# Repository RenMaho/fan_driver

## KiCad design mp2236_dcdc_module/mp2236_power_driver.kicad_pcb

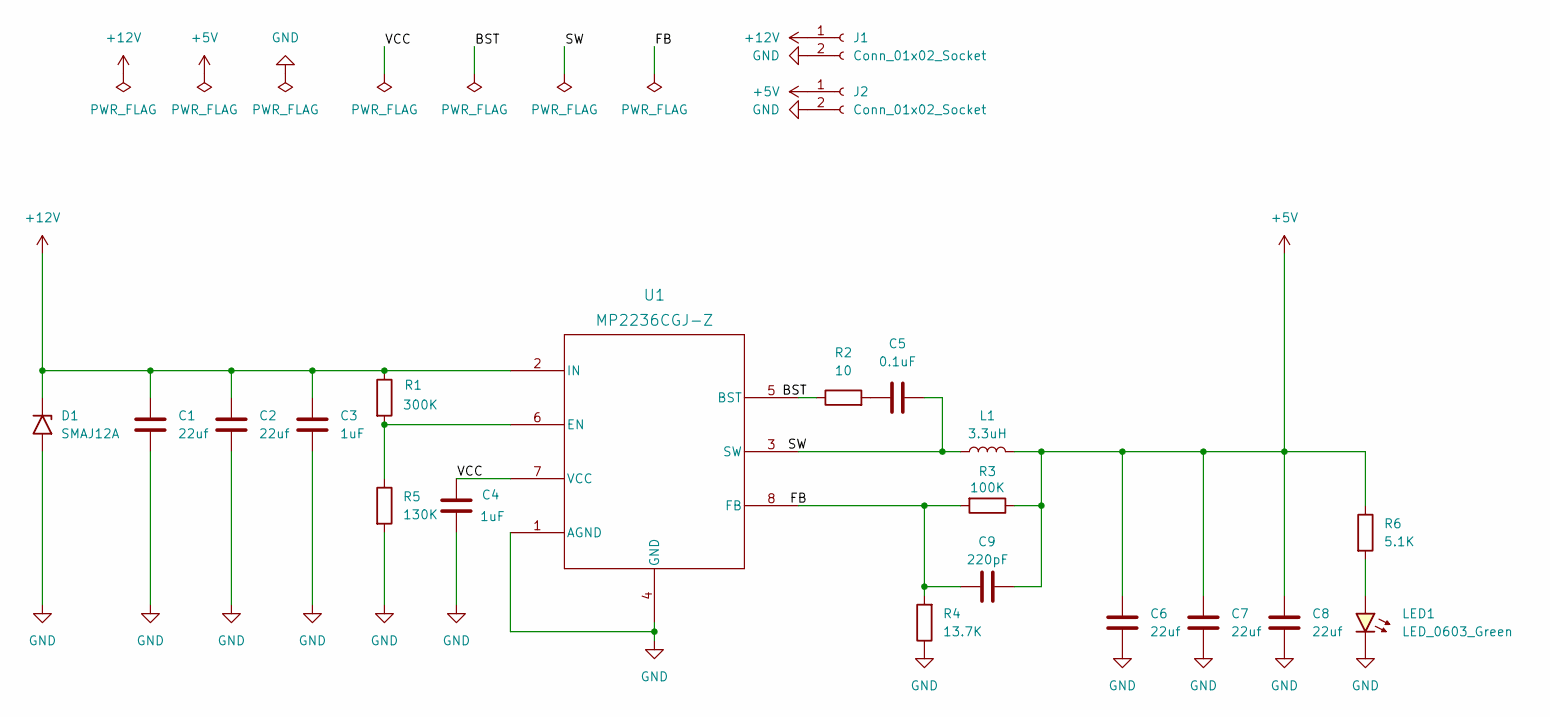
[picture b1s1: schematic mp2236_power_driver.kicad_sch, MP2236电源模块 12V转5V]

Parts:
C1, C2: 22uf; C_1206_3216Metric
C3, C4: 1uF; C_0603_1608Metric
C5: 0.1uF; C_0603_1608Metric
C6, C7, C8: 22uf; C_0805_2012Metric
C9: 220pF; C_0603_1608Metric
D1: SMAJ12A; D_SMA
J1, J2: Conn_01x02_Socket; 4mmx5mm_2x18.0mm power pad
L1: 3.3uH; L_Abracon_ASPI-0630LR
LED1: LED_0603_Green; LED_0603_1608Metric
R1: 300K; R_0603_1608Metric
R2: 10; R_0603_1608Metric
R3: 100K; R_0603_1608Metric
R4: 13.7K; R_0603_1608Metric
R5: 130K; R_0603_1608Metric
R6: 5.1K; R_0603_1608Metric
U1: MP2236CGJ-Z; TSOT-23-8

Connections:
+5V: C6.1, C7.1, C8.1, C9.1, J2.1, L1.2, R3.1, R6.1
+12V: C1.1, C2.1, C3.1, D1.1 (A1), J1.1, R1.1, U1.2 (IN)
/BST: R2.1, U1.5 (BST)
/FB: C9.2, R3.2, R4.2, U1.8 (FB)
/SW: C5.2, L1.1, U1.3 (SW)
/VCC: C4.2, U1.7 (VCC)
GND: C1.2, C2.2, C3.2, C4.1, C6.2, C7.2, C8.2, D1.2 (A2), J1.2, J2.2, LED1.1 (K), R4.1, R5.2, U1.1 (AGND), U1.4 (GND)
unnamed: C5.1, R2.2
unnamed: LED1.2 (A), R6.2
unnamed: R1.2, R5.1, U1.6 (EN)

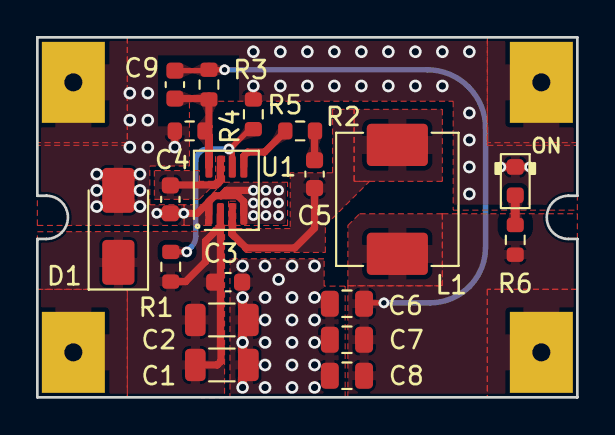
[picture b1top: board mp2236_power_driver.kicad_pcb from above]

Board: 2 copper layers, 30.0 x 20.0 mm, 21 parts (0 on the bottom side), 10 nets.

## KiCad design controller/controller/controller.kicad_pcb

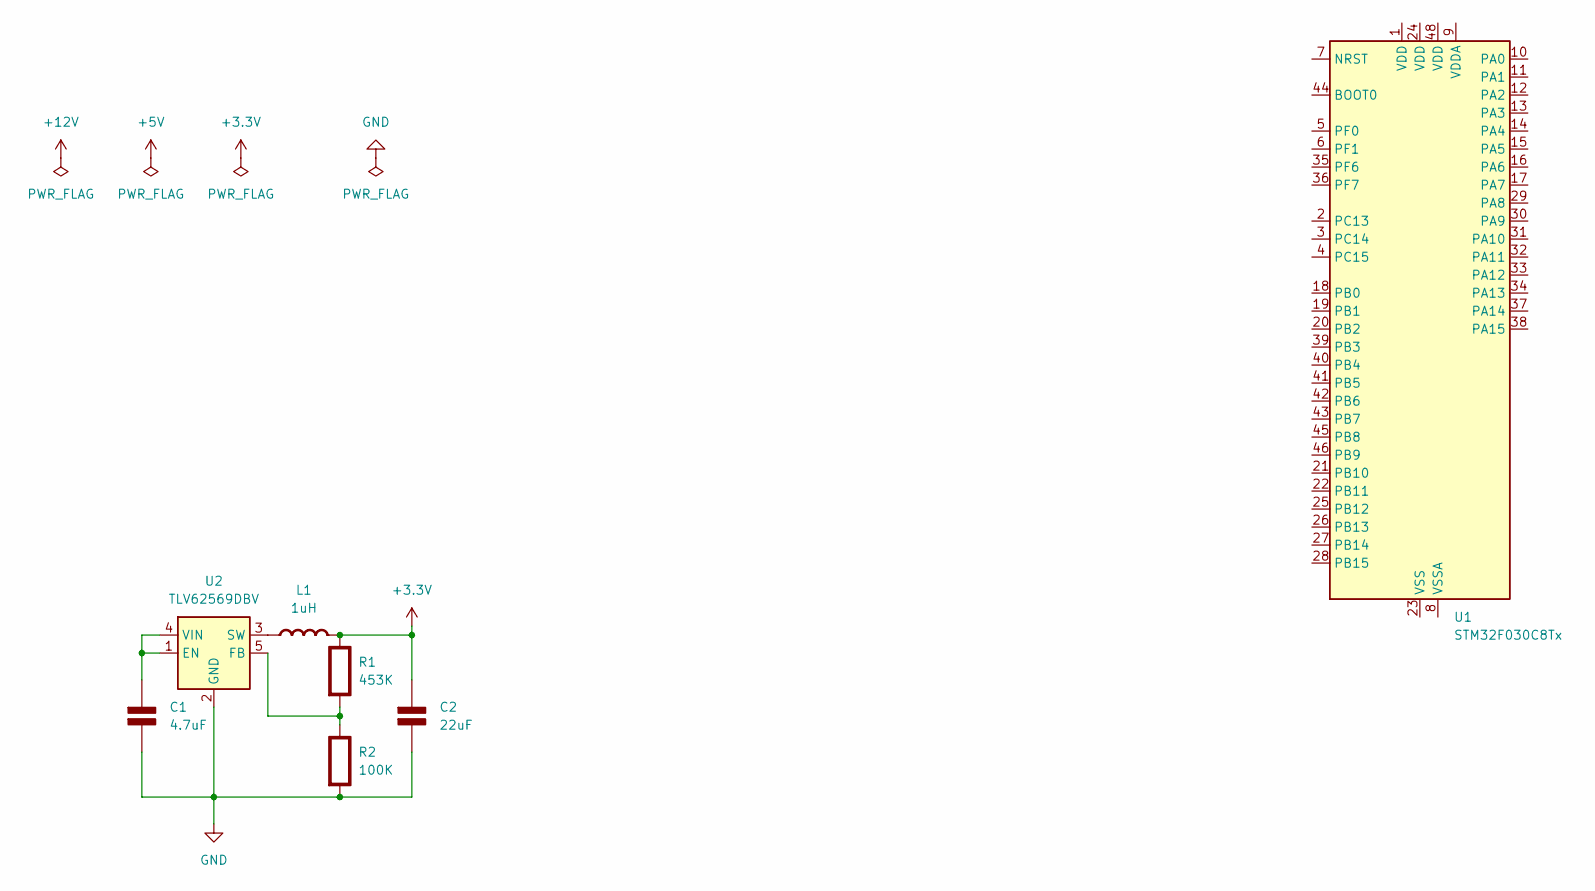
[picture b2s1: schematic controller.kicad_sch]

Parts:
C1: 4.7uF; C_0805_2012Metric_Pad1.18x1.45mm_HandSolder; Rating V
C2: 22uF; C_0805_2012Metric_Pad1.18x1.45mm_HandSolder; Rating V
L1: 1uH; L_Abracon_ASPI-0630LR; Rating A
R1: 453K; R_0603_1608Metric_Pad0.98x0.95mm_HandSolder; Rating W
R2: 100K; R_0603_1608Metric_Pad0.98x0.95mm_HandSolder; Rating W
U1: STM32F030C8Tx; LQFP-48_7x7mm_P0.5mm
U2: TLV62569DBV; SOT-23-5

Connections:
+3.3V: C2.1 (+), L1.2 (-), R1.1 (+)
GND: C1.2 (-), C2.2 (-), R2.2 (-), U2.2 (GND)
unnamed: C1.1 (+), U2.1 (EN), U2.4 (VIN)
unnamed: L1.1 (+), U2.3 (SW)
unnamed: R1.2 (-), R2.1 (+), U2.5 (FB)
unnamed: U1.23 (VSS), U1.47 (VSS)

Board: 2 copper layers, 7 parts (0 on the bottom side), 6 nets, no tracks yet.

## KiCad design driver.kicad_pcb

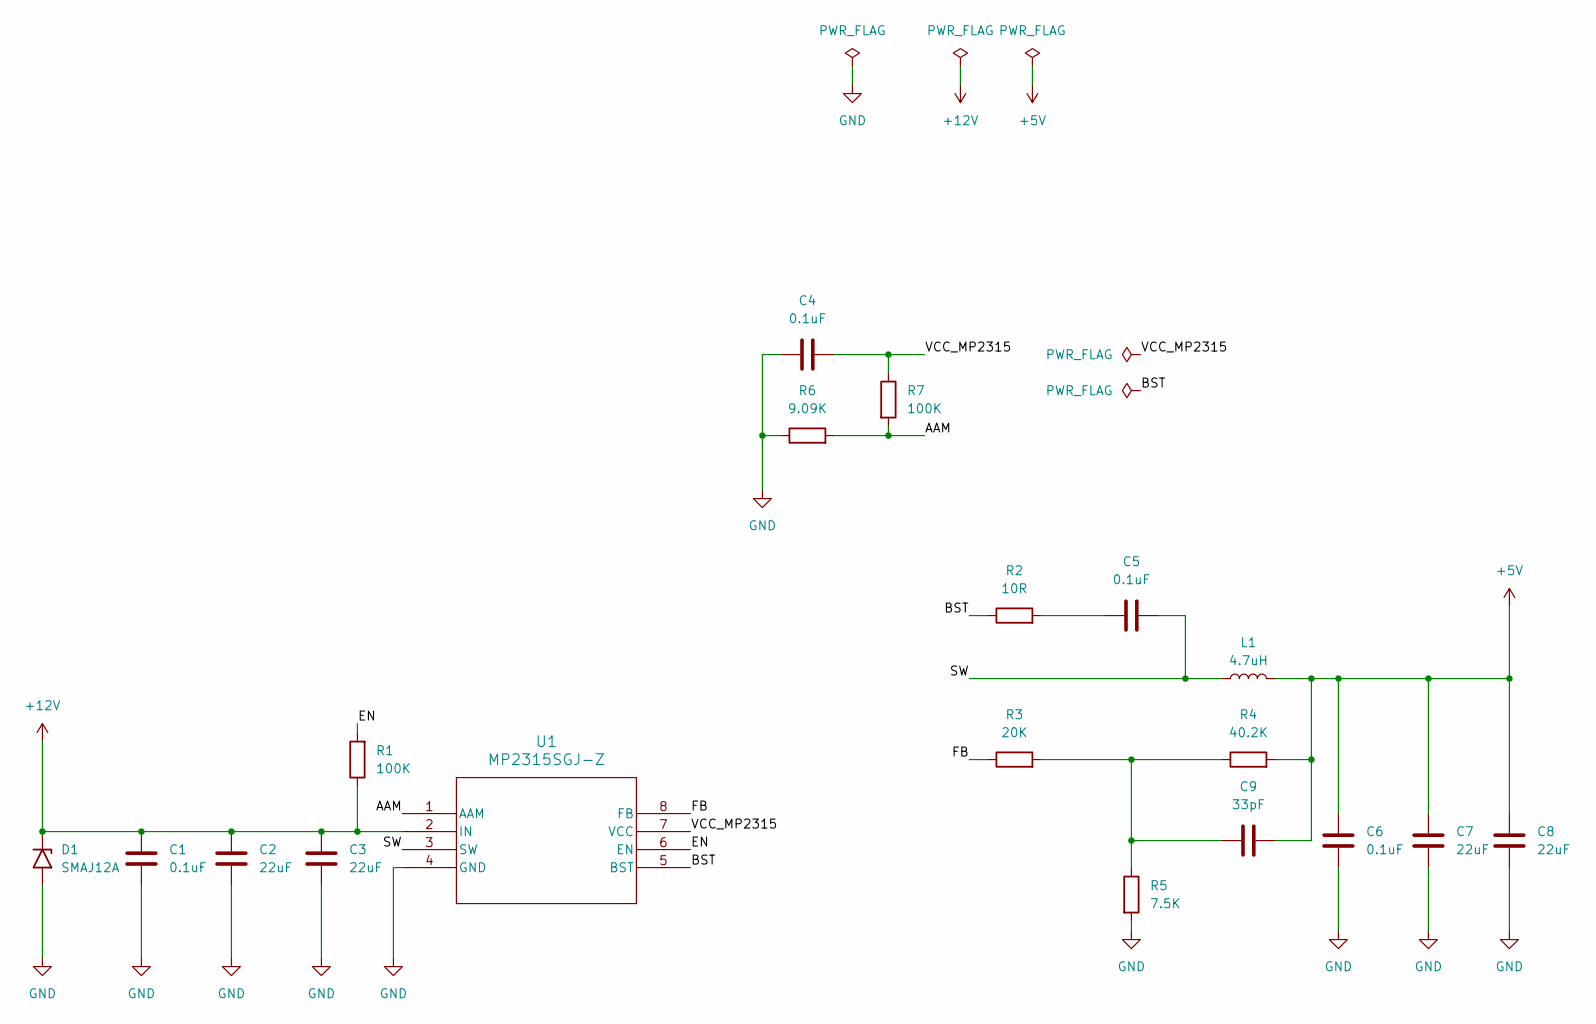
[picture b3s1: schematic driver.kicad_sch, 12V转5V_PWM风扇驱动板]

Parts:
C1, C4, C5, C6: 0.1uF; C_0805_2012Metric_Pad1.18x1.45mm_HandSolder
C2, C3, C7, C8: 22uF; C_1206_3216Metric_Pad1.33x1.80mm_HandSolder
C9: 33pF; C_0805_2012Metric_Pad1.18x1.45mm_HandSolder
D1: SMAJ12A; D_SMA
L1: 4.7uH; L_Changjiang_FXL0630
R1, R7: 100K; R_0805_2012Metric_Pad1.20x1.40mm_HandSolder
R2: 10R; R_0805_2012Metric_Pad1.20x1.40mm_HandSolder
R3: 20K; R_0805_2012Metric_Pad1.20x1.40mm_HandSolder
R4: 40.2K; R_0805_2012Metric_Pad1.20x1.40mm_HandSolder
R5: 7.5K; R_0805_2012Metric_Pad1.20x1.40mm_HandSolder
R6: 9.09K; R_0805_2012Metric_Pad1.20x1.40mm_HandSolder
U1: MP2315SGJ-Z; TSOT-23-8_HandSoldering

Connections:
+5V: C6.1, C7.1, C8.1, C9.2, L1.2, R4.2
+12V: C1.1, C2.1, C3.1, D1.1 (A1), R1.1, U1.2 (IN)
/AAM: R6.2, R7.2, U1.1 (AAM)
/BST: R2.1, U1.5 (BST)
/EN: R1.2, U1.6 (EN)
/FB: R3.1, U1.8 (FB)
/SW: C5.2, L1.1, U1.3 (SW)
/VCC_MP2315: C4.2, R7.1, U1.7 (VCC)
GND: C1.2, C2.2, C3.2, C4.1, C6.2, C7.2, C8.2, D1.2 (A2), R5.2, R6.1, U1.4 (GND)
unnamed: C5.1, R2.2
unnamed: C9.1, R3.2, R4.1, R5.1

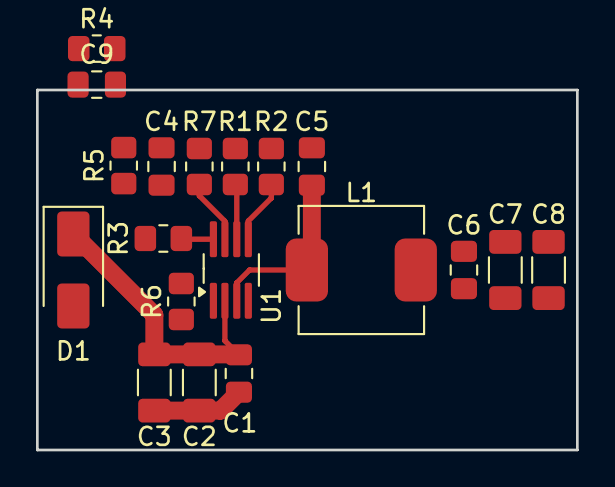
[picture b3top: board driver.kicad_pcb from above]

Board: 2 copper layers, 30.0 x 20.0 mm, 19 parts (0 on the bottom side), 11 nets.

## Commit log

2024-12-06 MP2315S layout
2024-12-08 add datasheet
2024-12-08 mp2236 power board
2024-12-12 version 1.0
2024-12-12 changed `mp2236_power_driver` to `mp2236_dcdc_module`
2024-12-15 add tlv62569 datasheet
2024-12-31 mp2236 power module v1.1
